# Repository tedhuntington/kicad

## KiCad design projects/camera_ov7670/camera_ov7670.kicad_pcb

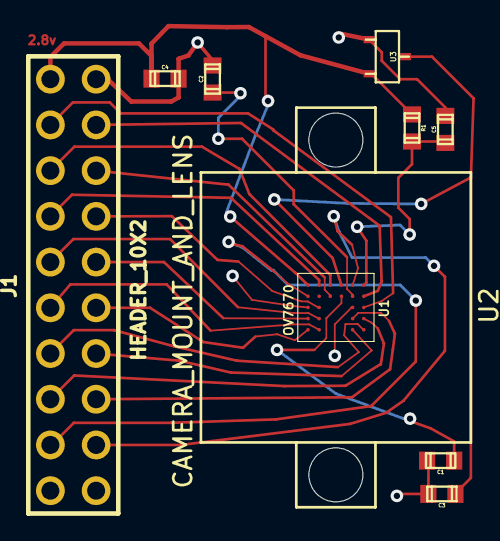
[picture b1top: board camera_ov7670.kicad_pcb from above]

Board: 2 copper layers, 10 parts (0 on the bottom side), 22 nets.

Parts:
C1, C2: .1uF; TED_SM0603
C3, C4, C5: 4.7uF; TED_SM0603
J1: HEADER_10X2; TED_HEADER_10x2_BOTTOM_SIDE
R1: 10; TED_SM0603
U1: OV7670; TED_CSP2-24
U2: CAMERA_MOUNT_AND_LENS; TED_CAMERA_M12x0.5_mount
U3: REGULATOR_1.8V; TED_SC59

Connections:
+1.8v: C3.1, U1.C1, U3.2
+2.8v: C4.1, J1.1, R1.1, U1.F1, U3.3
AVDD: C5.1, R1.2, U1.A1
D0: J1.13, U1.B4
D1: J1.8, U1.A4
D2: J1.14, U1.B5
D3: J1.7, U1.A5
D4: J1.15, U1.F5
D5: J1.6, U1.E5
D6: J1.16, U1.F4
D7: J1.5, U1.E4
GND: C1.2, C2.2, C3.2, C4.2, C5.2, J1.20, U1.B3, U1.F3, U3.1
HREF: J1.18, U1.D2
unnamed: C2.1, U1.B2
unnamed: C1.1, U1.C2
PCLK: J1.4, U1.E1
PWDN: J1.12, U1.B1
RESET: J1.9, U1.F2
SIO_C: J1.2, U1.A3
SIO_D: J1.19, U1.A2
VSYNC: J1.3, U1.D1
XCLK: J1.17, U1.E3

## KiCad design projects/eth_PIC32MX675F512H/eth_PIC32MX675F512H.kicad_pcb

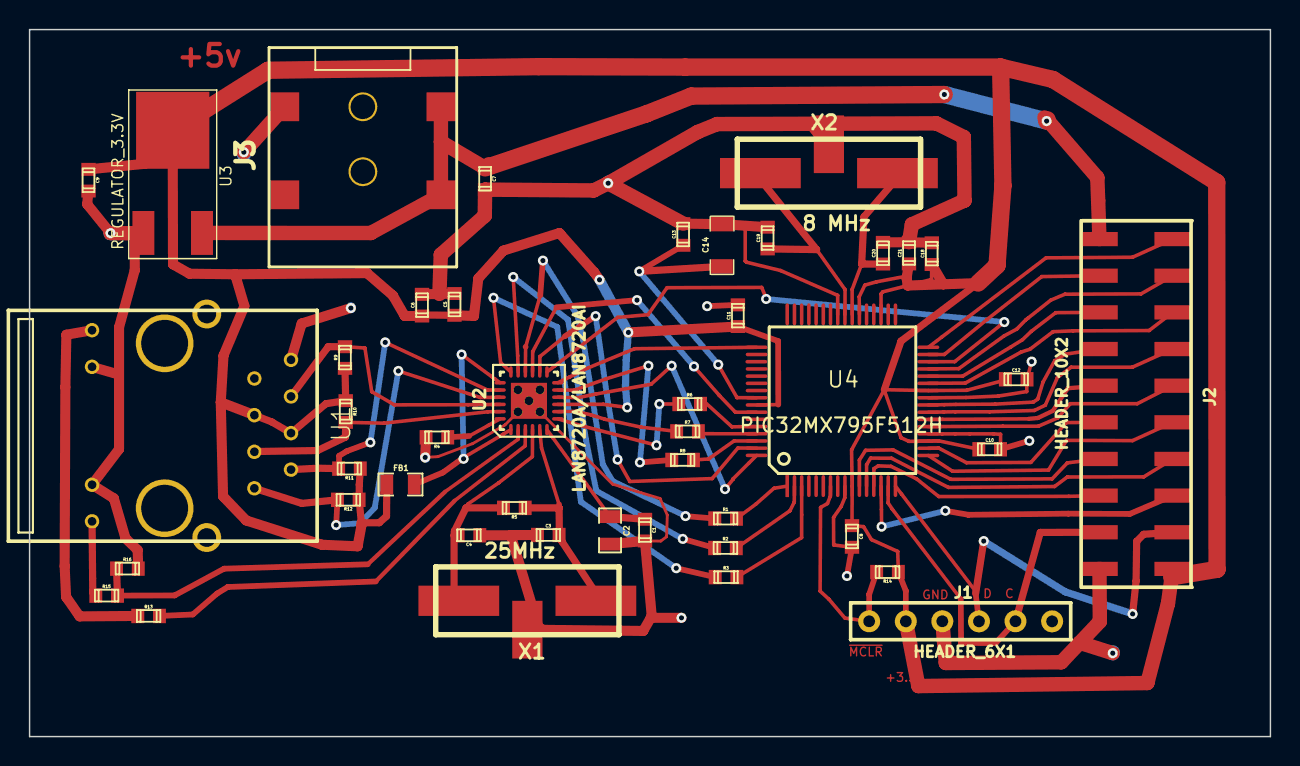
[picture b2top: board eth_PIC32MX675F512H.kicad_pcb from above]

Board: 2 copper layers, 86.0 x 49.0 mm, 44 parts (0 on the bottom side), 54 nets.

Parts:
C1, C5, C6, C8, C10, C11, C12, C13, C18, C21: .1uF; TED_SM0603
C2: 1uF; TED_SM0805
C3, C4, C19, C20: 18pF; TED_SM0603
C7, C9: 4.7uF; TED_SM0603
C14: 10uF; TED_SM1206
FB1: 500mA; TED_SM0805
J1: HEADER_6X1; TED_HEADER_6x1_BOTTOM
J2: HEADER_10X2; TED_HEADER_10x2_SMT
J3: Logic DC_2.1MM; TED_DC_2.1mm_SMT
R1, R2, R3, R6, R7, R8: 33; TED_SM0603
R4: 12.1k 1%; TED_SM0603
R5: 1M; TED_SM0603
R9, R10, R11, R12: 49.9; TED_SM0603
R13, R15: 249; TED_SM0603
R14: 4.7k; TED_SM0603
R16: 10k 1%; TED_SM0603
U1: RJ45_12_PIN; TED_RJ45_12pin_Bottom
U2: LAN8720A/LAN8720AI; TED_QFN24
U3: REGULATOR_3.3V; TED_3v_DPAK
U4: PIC32MX795F512H; TQFP_64
X1: 25MHz; TED_crystal_W_GND_SMT_13x5mm
X2: 8 MHz; TED_crystal_W_GND_SMT_13x5mm

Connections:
+3.3v: C5.1, C6.1, C8.1, C9.1, C10.1, C11.1, C12.1, C18.1, C21.1, FB1.1, J1.2, J2.1, R9.1, R10.1, R11.1, R12.1, R14.1, U1.4, U1.5, U2.9, U3.2, U4.10, U4.19, U4.26, U4.35, U4.38, U4.57
+5v: C7.1, J2.11, J3.1, U3.3
AVDD: FB1.2, U2.1, U2.19
ECRSDV: R8.2, U4.62
EMDC: U2.13, U4.30
EMDIO: U2.12, U4.49
EREFCLK: U2.14, U4.63
ERXD0: R7.2, U4.61
ERXD1: R6.2, U4.60
ERXERR: U2.10, U4.64
ETXD0: R2.2, U4.2
ETXD1: R3.2, U4.3
ETXEN: R1.2, U4.1
GND: C1.2, C2.2, C3.1, C4.1, C5.2, C6.2, C7.2, C8.2, C9.2, C10.2, C11.2, C12.2, C13.2, C14.2, C18.2, C19.2, C20.2, C21.2, J1.3, J2.20, J3.2, R4.2, R16.2, U1.8, U1.10, U1.11, U2.25, U3.1, U4.9, U4.20, U4.25, U4.41, X1.3, X2.3
GreenLED: R15.1, U1.9
ICSPCLK_RB1: J1.5, J2.19, U4.15
ICSPDAT_RB0: J1.4, J2.2, U4.16
unnamed: R13.2, U2.3
unnamed: C3.2, R5.1, U2.5, X1.1
unnamed: C4.2, R5.2, U2.4, X1.2
unnamed: C1.1, C2.1, U2.6
unnamed: R7.1, U2.8
unnamed: R6.1, U2.7
unnamed: R4.1, U2.24
unnamed: R15.2, R16.1, U2.2
unnamed: C19.1, U4.40, X2.1
unnamed: R1.1, U2.16
unnamed: R2.1, U2.17
unnamed: R3.1, U2.18
unnamed: R8.1, U2.11
unnamed: C13.1, C14.1, U4.56
unnamed: C20.1, U4.39, X2.2
RB2: J2.3, U4.14
RB3: J2.18, U4.13
RB4: J2.4, U4.12
RB5: J2.17, U4.11
RB6: J2.5, U4.17
RB7: J2.16, U4.18
RB8: J2.6, U4.21
RB9: J2.15, U4.22
RB10: J2.7, U4.23
RB11: J2.14, U4.24
RB12: J2.8, U4.27
RB13: J2.13, U4.28
RB14: J2.9, U4.29
RF4: J2.12, U4.31
RF5: J2.10, U4.32
RXN: R9.2, U1.6, U2.22
RXP: R10.2, U1.3, U2.23
TXN: R11.2, U1.2, U2.20
TXP: R12.2, U1.1, U2.21
YellowLED: R13.1, U1.12
nRST: U2.15, U4.58
~MCLR~: J1.1, R14.2, U4.7

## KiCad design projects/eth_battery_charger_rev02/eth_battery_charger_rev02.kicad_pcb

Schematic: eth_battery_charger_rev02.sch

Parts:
C1, C2, C3, C4, C5, C6, C7, C8: 4.7uF
D1, D2, D3, D4: LED
H1, H2: HOLE
J1, J2, J3, J4, J5: DC_2.1MM; TED_DC_2.1mm
R1: 1k 1%
R2, R3, R4: 1k
R5, R6, R7, R8: 150
U1, U2, U3, U4: MCP73113

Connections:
GND: C1.2, C2.2, C3.2, C4.2, C5.2, C6.2, C7.2, C8.2, J1.2, J2.2, J3.2, J4.2, J5.2, R1.2, R2.2, R3.2, R4.2, U1.8 (VSS), U1.9 (VSS), U1.11 (EP), U2.8 (VSS), U2.9 (VSS), U2.11 (EP), U3.8 (VSS), U3.9 (VSS), U3.11 (EP), U4.8 (VSS), U4.9 (VSS), U4.11 (EP)
unnamed: D3.2 (A), R7.2
unnamed: D2.2 (A), R6.2
unnamed: D1.2 (A), R5.2
unnamed: D4.2 (A), R8.2
PROG1: R1.1, U1.10 (PROG)
PROG2: R2.1, U2.10 (PROG)
PROG3: R3.1, U3.10 (PROG)
PROG4: R4.1, U4.10 (PROG)
STAT1: D3.1 (K), U1.7 (STAT)
STAT2: D1.1 (K), U2.7 (STAT)
STAT3: D2.1 (K), U3.7 (STAT)
STAT4: D4.1 (K), U4.7 (STAT)
VBAT1: C1.1, J2.1, U1.3 (VBAT), U1.4 (VBAT)
VBAT2: C2.1, J3.1, U2.3 (VBAT), U2.4 (VBAT)
VBAT3: C3.1, J4.1, U3.3 (VBAT), U3.4 (VBAT)
VBAT4: C4.1, J5.1, U4.3 (VBAT), U4.4 (VBAT)
VDD: C5.1, C6.1, C7.1, C8.1, J1.1, R5.1, R6.1, R7.1, R8.1, U1.1 (VDD), U1.2 (VDD), U2.1 (VDD), U2.2 (VDD), U3.1 (VDD), U3.2 (VDD), U4.1 (VDD), U4.2 (VDD)

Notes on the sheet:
VDD=5v
AC adapter is 5V/5A

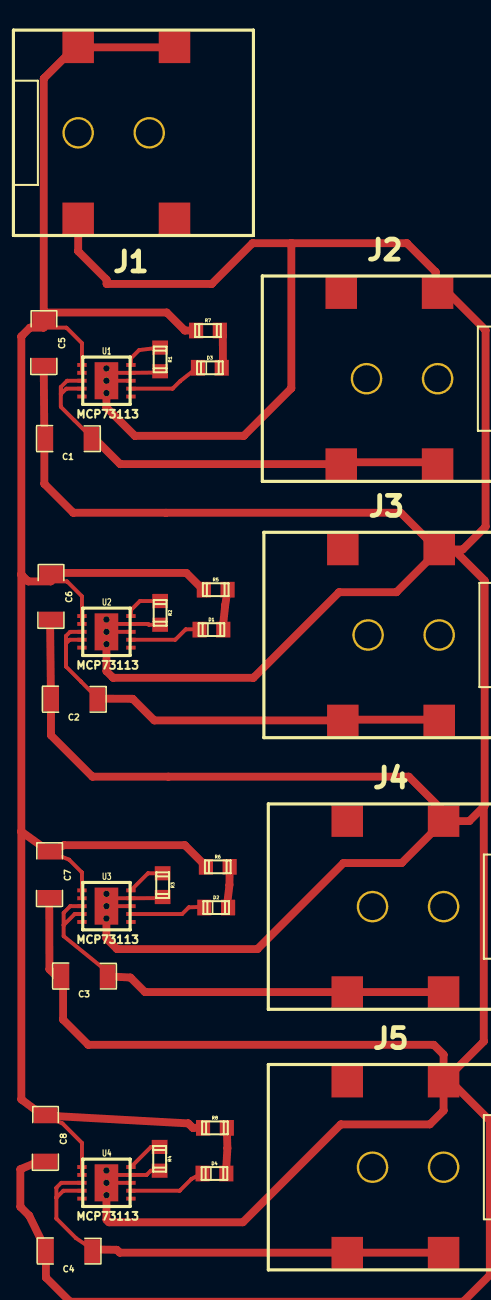
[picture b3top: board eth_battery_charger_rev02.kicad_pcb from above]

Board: 2 copper layers, 31 parts (0 on the bottom side), 18 nets.
